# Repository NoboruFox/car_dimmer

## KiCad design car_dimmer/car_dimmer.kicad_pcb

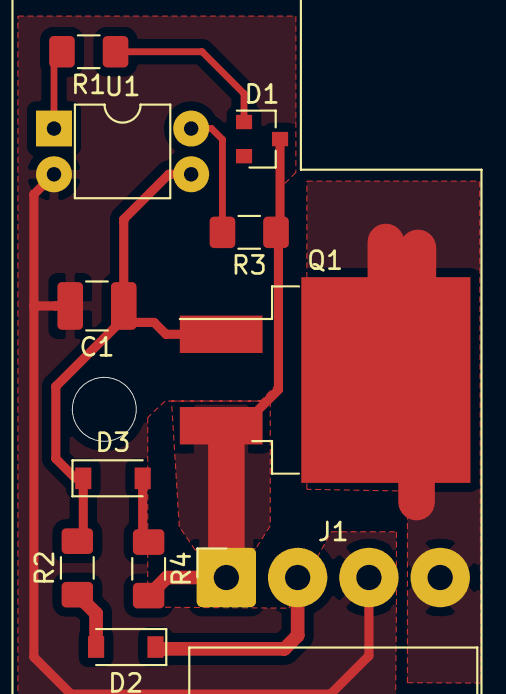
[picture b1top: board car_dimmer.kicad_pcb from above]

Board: 2 copper layers, 11 parts (0 on the bottom side), 10 nets.

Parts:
C1: 10u; R_1210_3225Metric_Pad1.42x2.65mm_HandSolder
D1: BZX84Cxx; D_SOT-23_ANK
D2, D3: 1N4148W; D_SOD-123
J1: Conn_01x04_Male; JST_VH_B4PS-VH_1x04_P3.96mm_Horizontal
Q1: IRF95305Spbf; TO-263-2
R1: 300; R_1206_3216Metric_Pad1.42x1.75mm_HandSolder
R2: 10K; R_1206_3216Metric_Pad1.42x1.75mm_HandSolder
R3: 56K; R_1206_3216Metric_Pad1.42x1.75mm_HandSolder
R4: 1M; R_1206_3216Metric_Pad1.42x1.75mm_HandSolder
U1: PC 123; DIP-4_W7.62mm

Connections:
+12V: D1.1, J1.1, Q1.3, R3.1, R4.2
DOOR: D2.1, J1.2
GND: C1.2, J1.3, U1.2
unnamed: C1.1, D3.1, Q1.1, R2.2, U1.3
unnamed: D1.2, R1.1
unnamed: D2.2, R2.1
unnamed: D3.2, R4.1
unnamed: R1.2, U1.1
unnamed: R3.2, U1.4
OUT: J1.4, Q1.2

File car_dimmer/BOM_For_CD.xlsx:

source3 | number4 | value | ref | value5 | footprint | datasheet | field | name6 | lib | part | description | names | tstamps7
 |  |  | D2 | 1N4148W | Diode_SMD:D_SOD-123 | https://www.vishay.com/docs/85748/1n4148w.pdf | https://www.chipdip.ru/product/mmsd4148 - 200мА | Альтернатива | Diode | 1N4148W | 75V 0.15A Fast Switching Diode, SOD-123 | / | /
 |  |  | D2 | 1N4148W | Diode_SMD:D_SOD-123 | https://www.vishay.com/docs/85748/1n4148w.pdf | https://www.chipdip.ru/product/1n4148w-5 | ЧиД | Diode | 1N4148W | 75V 0.15A Fast Switching Diode, SOD-123 | / | /
 | 1 уже есть | 2040 | U1 | PC 123 | Package_DIP:DIP-4_W7.62mm |  | https://www.chipdip.ru/product/pc123 | ЧиД | Isolator | SFH617A-1 | Optocoupler, Phototransistor Output, 5300 VRMS, VCEO 70V, CTR% 40-80, -55 to +1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 | / | /
 | 1 (20) | 9000079902 | R1 | 300 | Resistor_SMD:R_1206_3216Metric_Pad1.42x1.75mm_HandSolder | ~ | https://www.chipdip.ru/product0/9000079902 | ЧиД | Device | R | Resistor | / | /
 | 1 (20) | 9000079659 | R2 | 10K | Resistor_SMD:R_1206_3216Metric_Pad1.42x1.75mm_HandSolder | ~ | https://www.chipdip.ru/product0/9000079659 | ЧиД | Device | R | Resistor | / | /
 | 1 (20) есть уже | 9000079691 | R3 | 56K | Resistor_SMD:R_1206_3216Metric_Pad1.42x1.75mm_HandSolder | ~ | https://www.chipdip.ru/product0/9000079691 | ЧиД | Device | R | Resistor | / | /
 | 1 | 6916665003 | D1 | BZX84Cxx | Diode_SMD:D_SOT-23_ANK | https://diotec.com/tl_files/diotec/files/pdf/datasheets/bzx8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 | https://www.chipdip.ru/product/bzx84c13 | ЧиД | Diode | BZX84Cxx | 300mW Zener Diode, SOT-23 | / | /
 |  |  | J1 | Conn_01x04_Male | Connector_JST:JST_VH_B4PS-VH_1x04_P3.96mm_Horizontal | ~ | https://www.chipdip.ru/product/pwl-4r - 3.96 | Альтернатива | Connector | Conn_01x04_Male | Generic connector, single row, 01x04, script generated (kicad-library-utils/sch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 | / | /
 | 1 | 59183 | J1 | Conn_01x04_Male | Connector_JST:JST_VH_B4PS-VH_1x04_P3.96mm_Horizontal | ~ | https://www.chipdip.ru/product/pwl-4r - 3.96 | ЧиД | Connector | Conn_01x04_Male | Generic connector, single row, 01x04, script generated (kicad-library-utils/sch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 | / | /
 |  |  | Q1 | IRF95305Spbf | Package_TO_SOT_SMD:TO-263-2 |  | https://www.chipdip.ru/product/irf9540nspbf - 140W | Альтернатива | Transistor_FET | IRF9540N | -23A Id, -100V Vds, HEXFET P-Channel MOSFET, TO-220 | / | /
 | 1 | 9000013154 | Q1 | IRF95305Spbf | Package_TO_SOT_SMD:TO-263-2 |  | https://www.chipdip.ru/product/irf5305spbf | ЧиД | Transistor_FET | IRF9540N | -23A Id, -100V Vds, HEXFET P-Channel MOSFET, TO-220 | / | /
поставленный не подойдет - от 104шт | 1 (10) | 9000141173 | C1 | 10u | Resistor_SMD:R_1210_3225Metric_Pad1.42x2.65mm_HandSolder | ~ | https://www.chipdip.ru/product/grm32er6ya106ka12l - ceramic | ЧиД | Device | CP | Polarized capacitor | / | /
 | 1 (20) | 690816980 | R4 | 1M | Resistor_SMD:R_1206_3216Metric_Pad1.42x1.75mm_HandSolder | ~ | https://www.chipdip.ru/product0/690816980 | ЧиД | Device | R | Resistor | / | /
 |  |  | D3 | 1N4148W | Diode_SMD:D_SOD-123 | https://www.vishay.com/docs/85748/1n4148w.pdf | https://www.chipdip.ru/product/mmsd4148 - 200мА | Альтернатива | Diode | 1N4148W | 75V 0.15A Fast Switching Diode, SOD-123 | / | /
 | 2 | 9000461666 | D3 | 1N4148W | Diode_SMD:D_SOD-123 | https://www.vishay.com/docs/85748/1n4148w.pdf | https://www.chipdip.ru/product/1n4148w-5 | ЧиД | Diode | 1N4148W | 75V 0.15A Fast Switching Diode, SOD-123 | / | /
 | 1 | 51178 |  |  | PHU- 4 (DS1072-4 F), Розетка каб.с конт. 3.96мм |  | https://www.chipdip.ru/product/phu-4

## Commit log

2019-11-28 [WIP] created a car dimmer project
2019-11-29 [WIP]: Sch is drawn, need to finish and make pcb
2019-11-30 [WIP]: Schematic is done, PCB is routed and ready to final check
2019-12-01 [FEAT]: Finally checked
2019-12-06 [FEAT]: added a docs file with description of schematic
